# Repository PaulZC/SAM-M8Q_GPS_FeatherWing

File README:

###########################
# SAM-M8Q GPS FeatherWing #
###########################

A clone of the Adafruit Ultimate GPS FeatherWing but with the
u-blox SAM-M8Q replacing the GlobalTop FGPMMOPA6H

(PCBs are currently out for manufacture - should be assembled and tested before the end July 2017)

See SAM-M8Q_GPS_FeatherWing.pdf for the BOM etc.:
https://github.com/PaulZC/SAM-M8Q_GPS_FeatherWing/blob/master/SAM-M8Q_GPS_FeatherWing.pdf

The Arduino sub-directory contains code for the Adafruit M0 Feather Adalogger
https://www.adafruit.com/products/2796
which will log your route to SD card in GPX and CSV format

Based on an original design by Adafruit Industries:
https://www.adafruit.com/product/3133
https://github.com/adafruit/Adafruit-Ultimate-GPS-FeatherWing-PCB

Distributed under a Creative Commons Attribution, Share-Alike license

Adafruit invests time and resources providing this open source design,
please support Adafruit and open-source hardware by purchasing products from Adafruit!

Enjoy!

Paul

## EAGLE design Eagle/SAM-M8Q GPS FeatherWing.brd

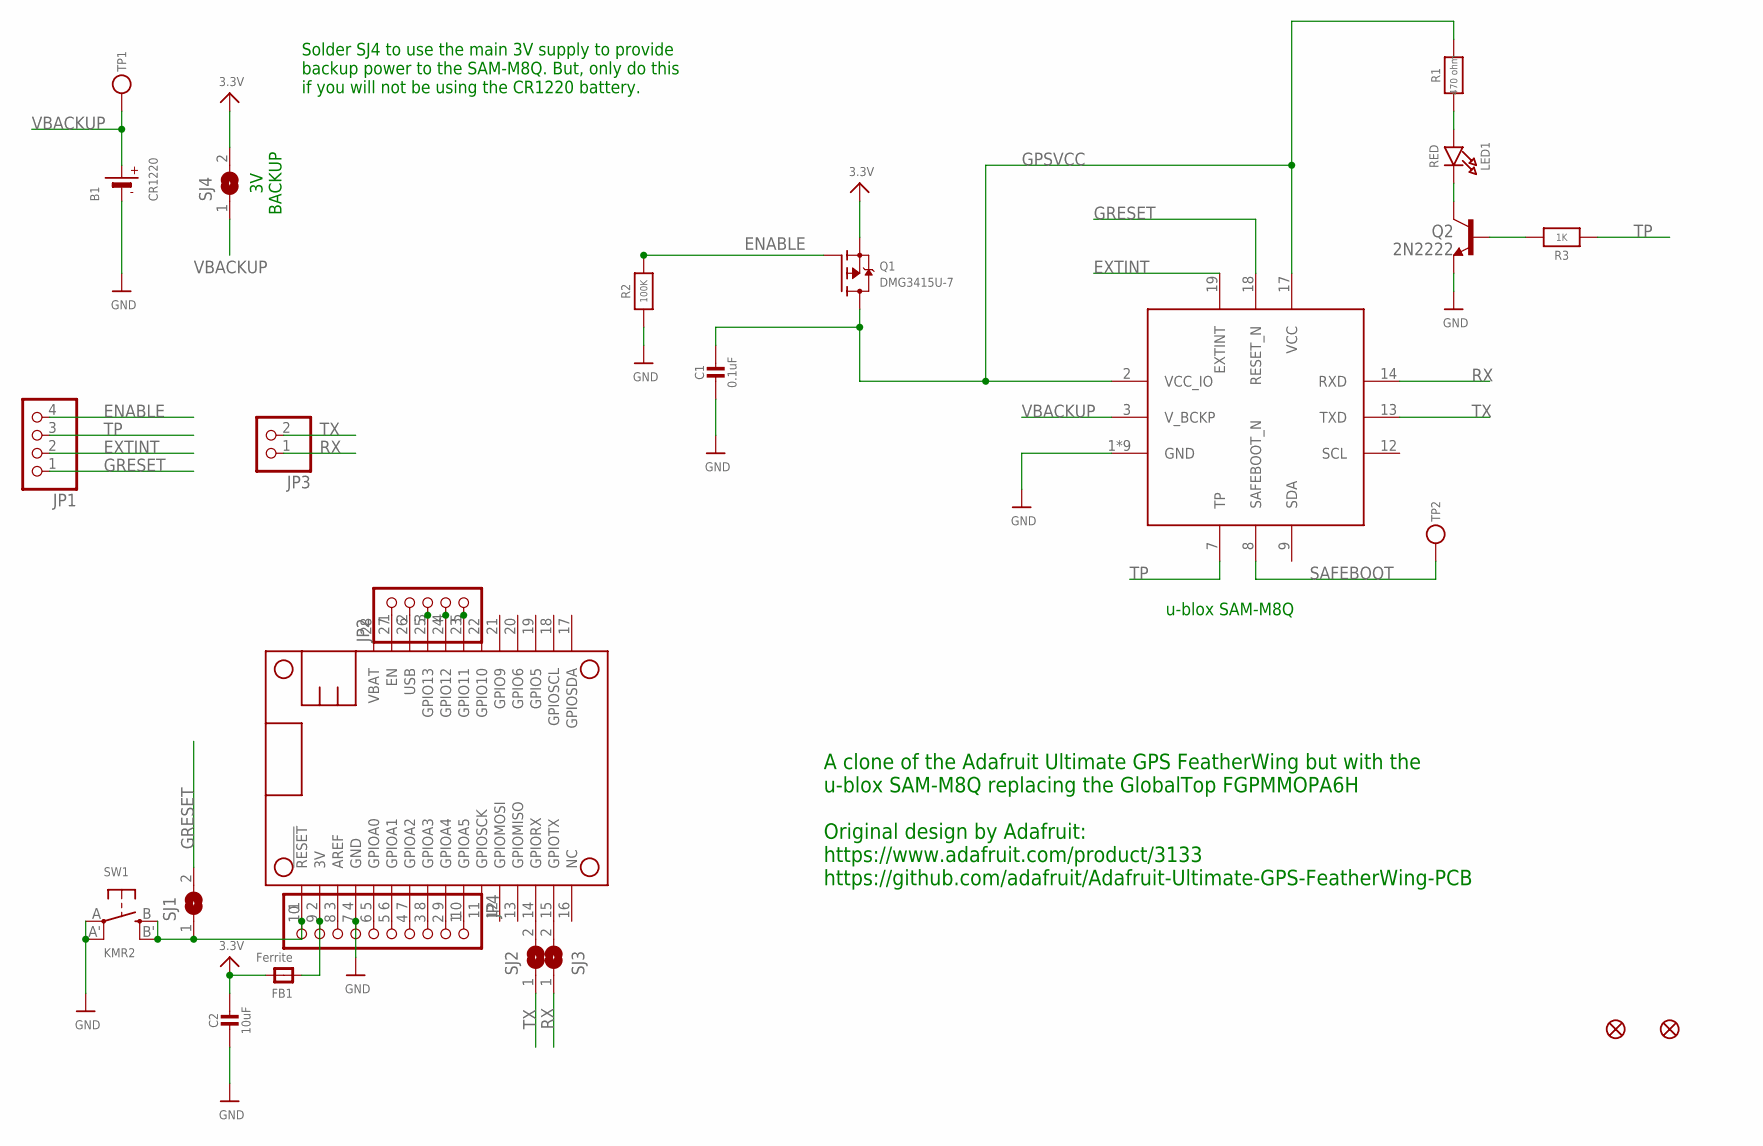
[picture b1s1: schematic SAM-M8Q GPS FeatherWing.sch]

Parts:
B1: CR1220; CR1220-2
C1: 0.1uF; 0805-NO
C2: 10uF; 0805-NO
FB1: Ferrite; 0805-NO
FID1, FID2: FIDUCIAL""; FIDUCIAL_1MM
JP1: HEADER-1X4ROUND; 1X04_ROUND
JP2: HEADER-1X570MIL; 1X05_ROUND_70
JP3: HEADER-1X2ROUND; 1X02_ROUND
JP4: HEADER-1X10ROUND; 1X10_ROUND
LED1: RED; CHIPLED_0805_NOOUTLINE
MS1: FEATHERWING
Q1: DMG3415U-7; SOT23-WIDE
Q2: 2N2222; SOT23-BEC
R1: 470 ohm; 0805-NO
R2: 100K; 0805-NO
R3: 1K; 0805-NO
SJ1, SJ4: SOLDERJUMPER; SOLDERJUMPER_ARROW_NOPASTE
SJ2, SJ3: SOLDERJUMPERCLOSED; SOLDERJUMPER_CLOSEDWIRE
SW1: KMR2; BTN_KMR2_4.6X2.8
TP1, TP2: TESTPOINTROUND1.5MM; TESTPOINT_ROUND_1.5MM
U1: SAM-M8Q

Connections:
3.3V: C2.1, FB1.2, Q1.2 (S), SJ4.2
3V: FB1.1, JP4.9, MS1.2 (3V)
ENABLE: JP1.4, Q1.1 (G), R2.2
EXTINT: JP1.2, U1.19 (EXTINT)
GND: B1.-, C1.2, C2.2, JP4.7, MS1.4 (GND), Q2.E, R2.1, SW1.A, SW1.A' (P1), U1.1 (GND), U1.4 (GND), U1.5 (GND), U1.6 (GND), U1.10 (GND), U1.11 (GND), U1.15 (GND), U1.16 (GND), U1.20 (GND)
GPSVCC: C1.1, Q1.3 (D), R1.2, U1.2 (VCC_IO), U1.17 (VCC)
GRESET: JP1.1, SJ1.2, U1.18 (RESET_N)
unnamed: JP2.3, MS1.25 (GPIO13)
unnamed: LED1.A, R1.1
unnamed: JP2.4, MS1.24 (GPIO12)
unnamed: LED1.C, Q2.C
unnamed: JP2.5, MS1.23 (GPIO11)
unnamed: JP4.1, MS1.10 (GPIOA5)
unnamed: JP4.2, MS1.9 (GPIOA4)
unnamed: JP4.3, MS1.8 (GPIOA3)
unnamed: JP4.4, MS1.7 (GPIOA2)
unnamed: JP4.5, MS1.6 (GPIOA1)
unnamed: JP4.6, MS1.5 (GPIOA0)
unnamed: JP4.10, MS1.1 (!RESET), SJ1.1, SW1.B (S), SW1.B' (S1)
unnamed: JP4.8, MS1.3 (AREF)
unnamed: JP2.1, MS1.27 (EN)
unnamed: MS1.14 (GPIORX), SJ2.2
unnamed: MS1.15 (GPIOTX), SJ3.2
unnamed: Q2.B, R3.2
RX: JP3.1, SJ3.1, U1.14 (RXD)
SAFEBOOT: TP2.P$1, U1.8 (SAFEBOOT_N)
TP: JP1.3, R3.1, U1.7 (TP)
TX: JP3.2, SJ2.1, U1.13 (TXD)
USB: JP2.2, MS1.26 (USB)
VBACKUP: B1.+, SJ4.1, TP1.P$1, U1.3 (V_BCKP)

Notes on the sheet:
A clone of the Adafruit Ultimate GPS FeatherWing but with the u-blox SAM-M8Q replacing the GlobalTop FGPMMOPA6H Original design by Adafruit: https://www.adafruit.com/product/3133 https://github.com/adafruit/Adafruit-Ultimate-GPS-FeatherWing-PCB
u-blox SAM-M8Q
3V BACKUP
Solder SJ4 to use the main 3V supply to provide backup power to the SAM-M8Q. But, only do this if you will not be using the CR1220 battery.

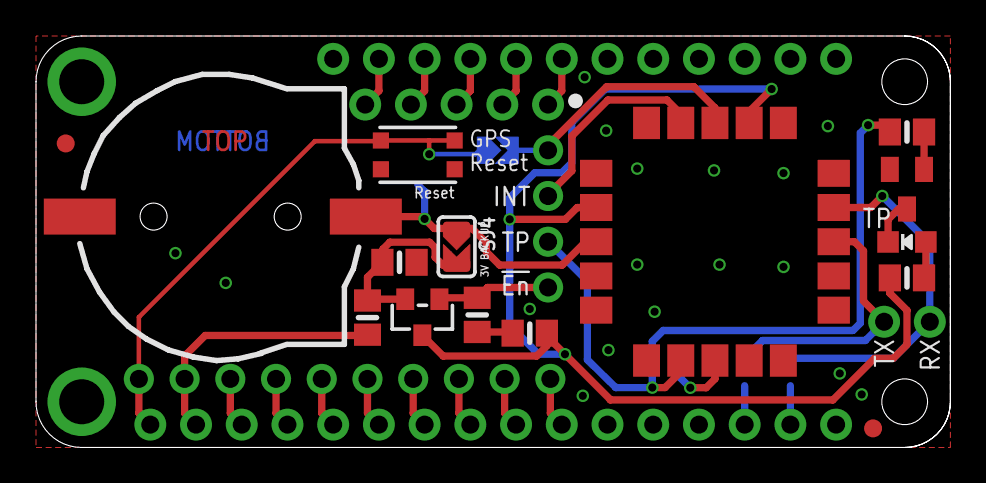
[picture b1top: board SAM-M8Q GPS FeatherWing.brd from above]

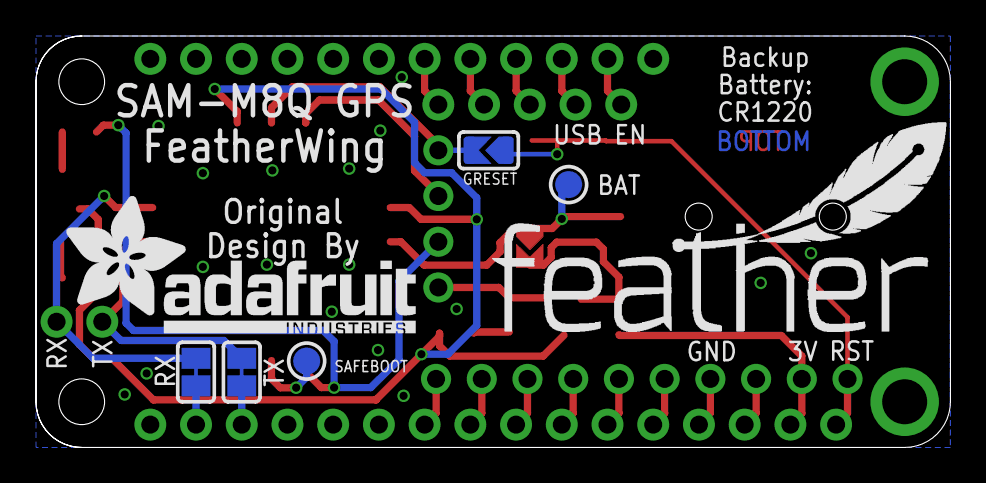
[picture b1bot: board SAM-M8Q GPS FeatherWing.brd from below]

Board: 2 copper layers, 50.8 x 22.9 mm, 26 parts (6 on the bottom side), 30 nets.

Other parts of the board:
U$11: ADAFRUIT_TEXT_20MM

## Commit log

2017-06-24 :confetti_ball: Added .gitattributes & .gitignore files
2017-06-24 First Release
    A clone of the Adafruit GPS FeatherWing incorporating the u-blox SAM-M8Q
    (built-in antenna)
2017-06-25 Minor tweaks. Included BOM.
2017-07-06 Updates
    Included the two fiducials in the tCream layer. Included Arduino code
    which runs on the Adafruit M0 Feather Adalogger which will log your
    route to SD card in GPX and CSV format.
2017-07-13 Tried and tested!
    Added images of the completed, tested PCB. Updated the README to match.
2017-07-13 Tried and Tested!
    Updated the readme
2017-07-13 Tried and tested!
    Updated the readme.md (again!)
2017-07-13 Tried and tested!
    Updated the readme.md (again again!)
2017-07-13 Tried and tested!
    Added links to the u-blox documentation
2017-08-14 Added HDOP logging
    Arduino code now logs HDOP in both GPX and CSV files
2017-09-03 Updated README.md, added LEARN.md
2017-09-03 Updated LEARN.md
2017-09-05 Updates
    Updated GPX-and_CSV_Logger to include a stop switch.
    Added the UBX command to enable Galileo reception.
    Updated LEARN.md to match.
2017-09-06 Minor updates
2017-09-06 Described how to enable Galileo reception
2017-09-20 Reduced vias. Added pad for SAFEBOOT.
2017-09-20 Updated the Arduino code.
    Updated the Arduino code. sendUBX now calculates the UBX packet
    checksums for you. Default GNSS is now GPS + Galileo + GLONASS + SBAS
2017-09-20 Added a via for SAFEBOOT
2017-09-20 Mentioned sendUBX in LEARN.md
    sendUBX now calculates the UBX packet checksums for you making it much
    easier to update the M8 configuration.
2017-09-20 Corrected the SAFEBOOT image filename
2017-09-20 Corrected the references for SAFEBOOT
2017-09-23 Added a test pad for safeboot
2017-09-23 Updated the schematic and overlays
2021-04-14 Add Gerbers
2022-10-01 Update license info
